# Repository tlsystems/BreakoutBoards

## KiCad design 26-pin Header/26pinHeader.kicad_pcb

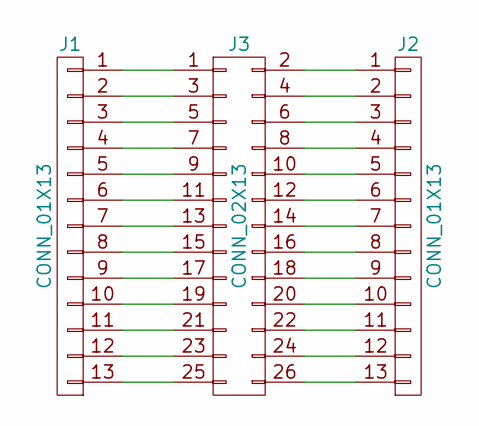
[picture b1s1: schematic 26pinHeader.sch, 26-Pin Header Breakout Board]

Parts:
J1, J2: CONN_01X13; Pin_Header_Straight_1x13_Pitch2.54mm
J3: CONN_02X13; Pin_Header_Straight_2x13_Pitch2.54mm

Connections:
unnamed: J1.1, J3.1
unnamed: J1.2, J3.3
unnamed: J1.3, J3.5
unnamed: J1.4, J3.7
unnamed: J1.5, J3.9
unnamed: J1.6, J3.11
unnamed: J1.7, J3.13
unnamed: J1.8, J3.15
unnamed: J1.9, J3.17
unnamed: J1.10, J3.19
unnamed: J1.11, J3.21
unnamed: J1.12, J3.23
unnamed: J1.13, J3.25
unnamed: J2.1, J3.2
unnamed: J2.2, J3.4
unnamed: J2.3, J3.6
unnamed: J2.4, J3.8
unnamed: J2.5, J3.10
unnamed: J2.6, J3.12
unnamed: J2.7, J3.14
unnamed: J2.8, J3.16
unnamed: J2.9, J3.18
unnamed: J2.10, J3.20
unnamed: J2.11, J3.22
unnamed: J2.12, J3.24
unnamed: J2.13, J3.26

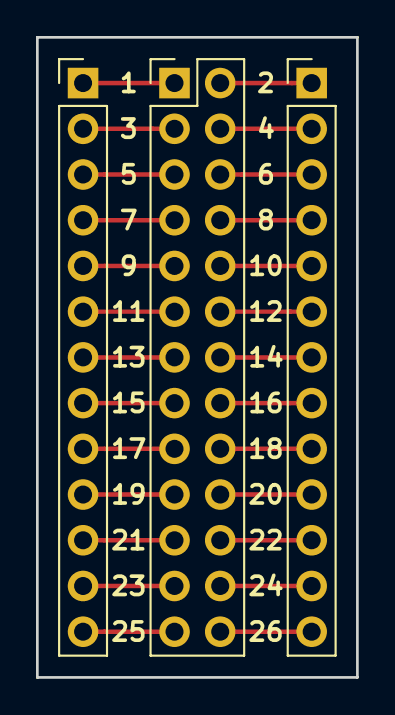
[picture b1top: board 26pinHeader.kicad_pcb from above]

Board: 2 copper layers, 17.8 x 35.6 mm, 3 parts (0 on the bottom side), 26 nets.

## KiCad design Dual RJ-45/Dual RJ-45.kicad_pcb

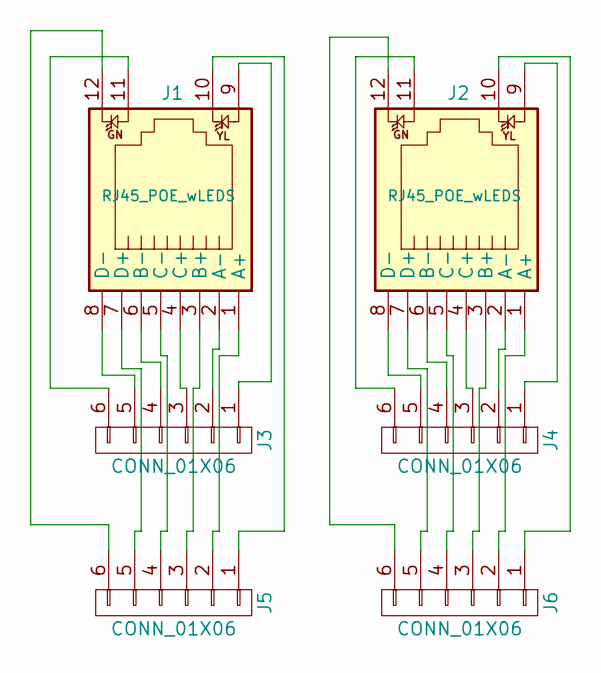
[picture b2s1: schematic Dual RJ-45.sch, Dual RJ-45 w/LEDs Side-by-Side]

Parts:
J1, J2: RJ45_POE_wLEDS; RJ45_POE_wLEDs
J3, J4, J5, J6: CONN_01X06; Pin_Header_Straight_1x06_Pitch2.54mm

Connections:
unnamed: J1.1 (A+), J5.2
unnamed: J1.2 (A-), J3.2
unnamed: J1.3 (B+), J5.3
unnamed: J1.4 (C+), J3.3
unnamed: J1.5 (C-), J5.4
unnamed: J1.6 (B-), J3.4
unnamed: J1.7 (D+), J5.5
unnamed: J1.8 (D-), J3.5
unnamed: J1.9, J3.1
unnamed: J1.10, J5.1
unnamed: J1.11, J3.6
unnamed: J1.12, J5.6
unnamed: J2.1 (A+), J6.2
unnamed: J2.2 (A-), J4.2
unnamed: J2.3 (B+), J6.3
unnamed: J2.4 (C+), J4.3
unnamed: J2.5 (C-), J6.4
unnamed: J2.6 (B-), J4.4
unnamed: J2.7 (D+), J6.5
unnamed: J2.8 (D-), J4.5
unnamed: J2.9, J4.1
unnamed: J2.10, J6.1
unnamed: J2.11, J4.6
unnamed: J2.12, J6.6

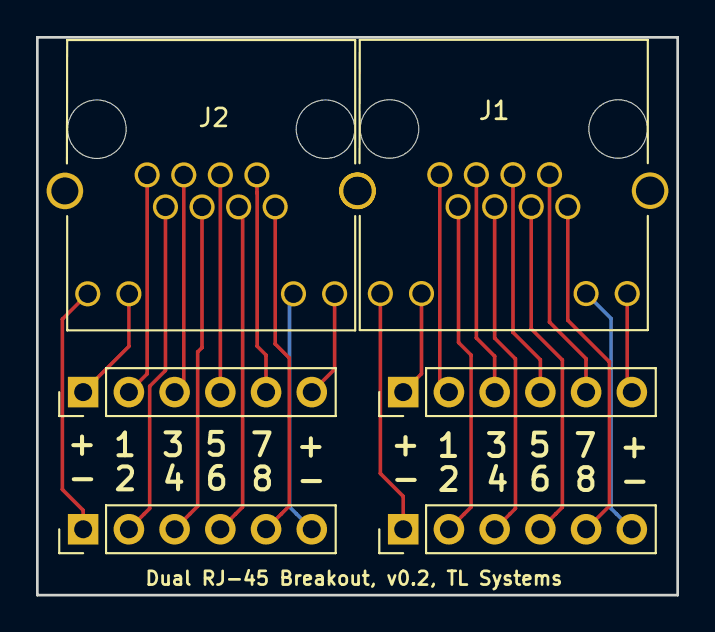
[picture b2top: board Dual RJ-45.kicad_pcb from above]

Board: 2 copper layers, 35.6 x 31.0 mm, 6 parts (0 on the bottom side), 24 nets.

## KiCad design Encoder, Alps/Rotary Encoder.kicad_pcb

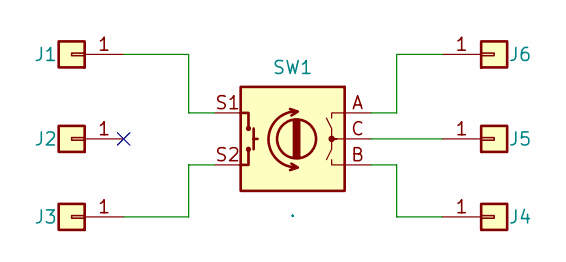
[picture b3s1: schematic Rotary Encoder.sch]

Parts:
J1, J2, J3, J4, J5, J6: PinHeader_1x01_P2.54mm_Vertical
SW1: .; QuadEncoder

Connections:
unnamed: J1.1, SW1.S1
unnamed: J3.1, SW1.S2
unnamed: J4.1, SW1.B
unnamed: J5.1, SW1.C
unnamed: J6.1, SW1.A

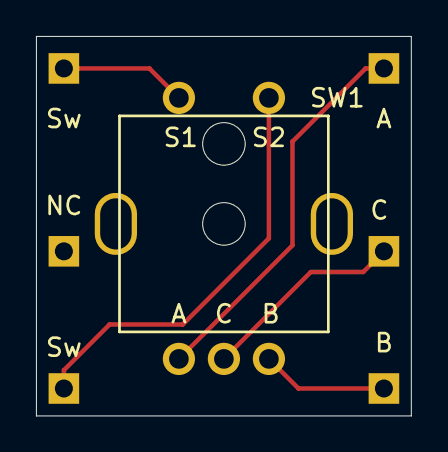
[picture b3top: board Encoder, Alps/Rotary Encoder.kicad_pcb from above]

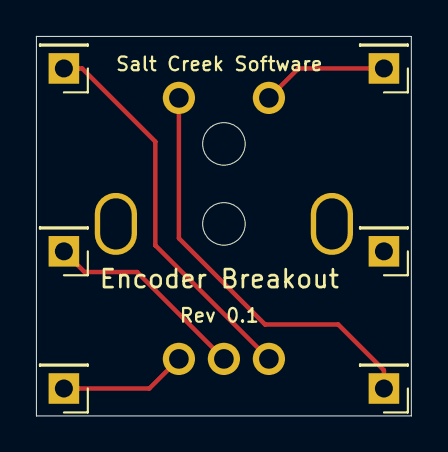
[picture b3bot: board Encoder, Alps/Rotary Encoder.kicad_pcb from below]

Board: 2 copper layers, 20.8 x 21.1 mm, 7 parts (6 on the bottom side), 5 nets.

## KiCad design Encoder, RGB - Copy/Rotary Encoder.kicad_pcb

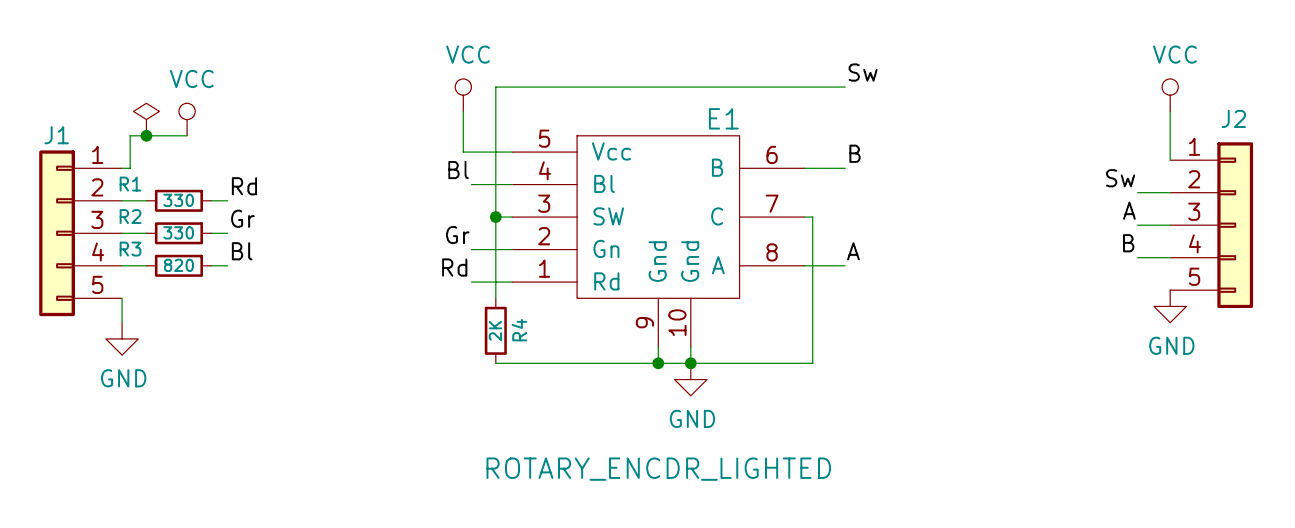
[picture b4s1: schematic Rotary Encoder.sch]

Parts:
E1: ROTARY_ENCDR_LIGHTED; QuadEncoder_withLEDS
J1, J2: Conn_01x05; PinHeader_1x05_P2.54mm_Vertical
R1, R2: 330; R_0805_2012Metric_Pad1.15x1.40mm_HandSolder
R3: 820; R_0805_2012Metric_Pad1.15x1.40mm_HandSolder
R4: 2K; R_0805_2012Metric_Pad1.15x1.40mm_HandSolder

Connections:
/A: E1.8 (A), J2.3
/B: E1.6 (B), J2.4
/Bl: E1.4 (Bl), R3.1
/Gr: E1.2 (Gn), R2.1
/Rd: E1.1 (Rd), R1.1
/Sw: E1.3 (SW), J2.2, R4.1
GND: E1.7 (C), E1.9 (Gnd), E1.10 (Gnd), J1.5, J2.5, R4.2
unnamed: J1.2, R1.2
unnamed: J1.3, R2.2
unnamed: J1.4, R3.2
VCC: E1.5 (Vcc), J1.1, J2.1

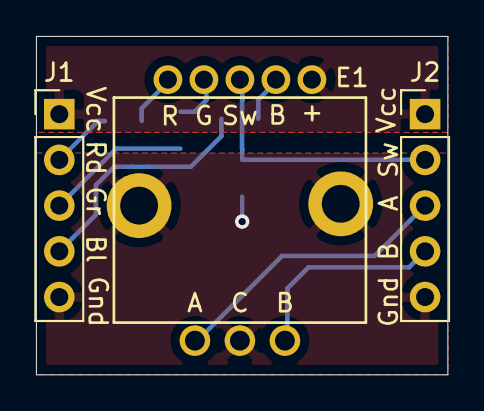
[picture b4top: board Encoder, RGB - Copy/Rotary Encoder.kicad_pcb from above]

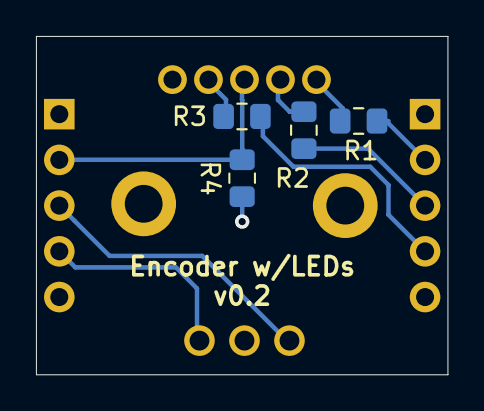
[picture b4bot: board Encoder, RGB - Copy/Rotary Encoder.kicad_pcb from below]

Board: 2 copper layers, 22.9 x 18.8 mm, 7 parts (4 on the bottom side), 11 nets.

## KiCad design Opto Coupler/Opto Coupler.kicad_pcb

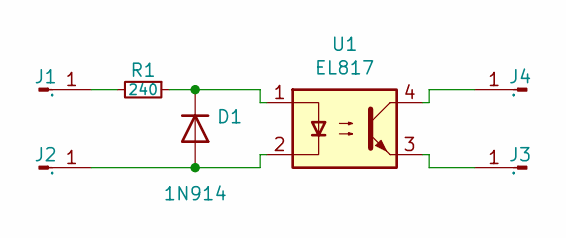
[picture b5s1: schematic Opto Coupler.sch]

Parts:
D1: 1N914; D_0603_1608Metric_Pad1.05x0.95mm_HandSolder
J1, J2, J3, J4: .; PinHeader_1x01_P2.54mm_Vertical
R1: 240; R_0603_1608Metric_Pad0.98x0.95mm_HandSolder
U1: EL817; Optek_K81xx

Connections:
unnamed: D1.1 (K), R1.1, U1.1
unnamed: D1.2 (A), J2.1, U1.2
unnamed: J1.1, R1.2
unnamed: J3.1, U1.3
unnamed: J4.1, U1.4

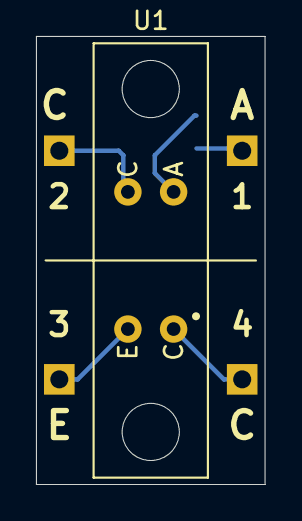
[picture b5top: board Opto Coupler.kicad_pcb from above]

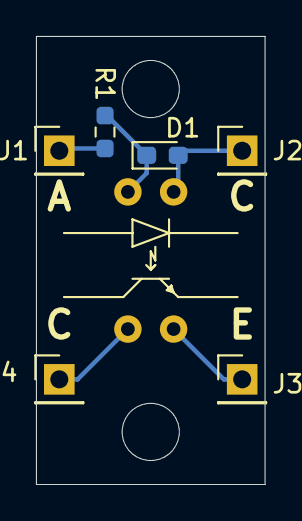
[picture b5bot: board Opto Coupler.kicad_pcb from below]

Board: 2 copper layers, 12.7 x 24.9 mm, 7 parts (6 on the bottom side), 5 nets.
